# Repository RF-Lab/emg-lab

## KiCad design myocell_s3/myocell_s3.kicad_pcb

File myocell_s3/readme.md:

# multiboard myocell-s3 design

ADC + CPU board for multiboard MYOCELL design. Includes [ADS1298(4)](https://static.chipdip.ru/lib/395/DOC009395274.pdf) and [ESP32-S3-WROOM-2](https://www.espressif.com/sites/default/files/documentation/esp32-s3-wroom-2_datasheet_en.pdf). Design based on ideas from [HeartyPatch](https://hackaday.io/project/21046-heartypatch-a-single-lead-ecg-hr-patch-with-esp32), [Adafruit Feather ESP32-S3](https://learn.adafruit.com/assets/110822), [electronics-homeassistant-lightscontroll
](https://github.com/crgarcia12/electronics-homeassistant-lightscontroll) etc.

## Revision history
 Sent to rezonit 2026.03.16

* BOM: [Interactive BOM ()](https://htmlpreview.github.io/?https://github.com/RF-Lab/emg-lab/blob/main/myocell_s3/bom/ibom.html)

### Top View

### Bottom View

## Gerbers

### Top+Silkscreen

### Inner 1 (under the top)

### Inner 2

### Bottom+Silkscreen

## Dependencies

* [Espressif KiCad Library](https://github.com/espressif/kicad-libraries)

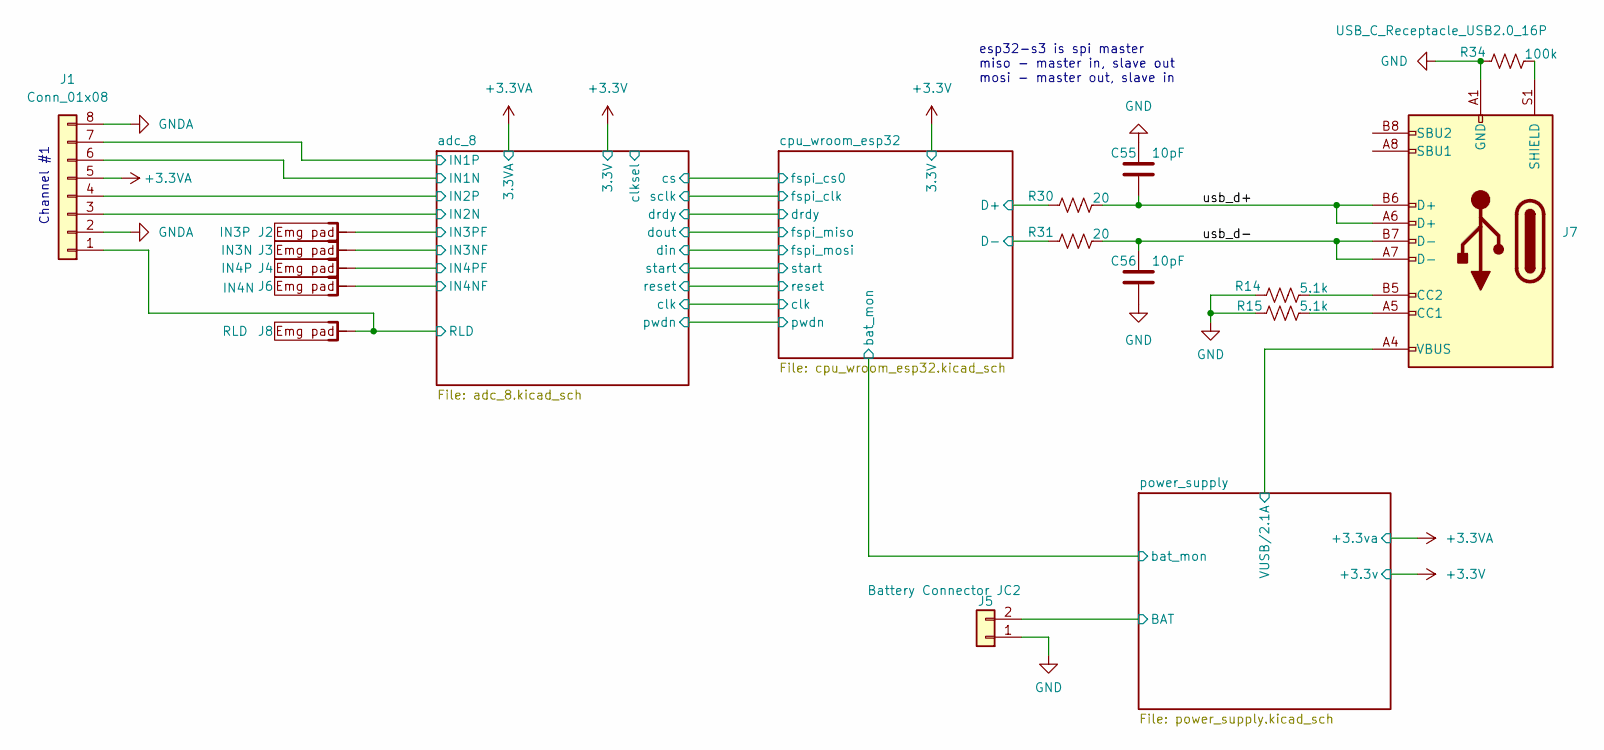
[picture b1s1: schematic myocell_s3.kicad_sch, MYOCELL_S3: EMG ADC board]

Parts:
C55, C56: 10pF; C_0805_2012Metric_Pad1.18x1.45mm_HandSolder
J1: Conn_01x08; Hirose_FH12-8S-0.5SH_1x08-1MP_P0.50mm_Horizontal
J2: IN3P; EMG_PAD_10_7
J3: IN3N; EMG_PAD_10_7
J4: IN4P; EMG_PAD_10_7
J5: Battery Connector JC2; JST_PH_S2B-PH-SM4-TB_1x02-1MP_P2.00mm_Horizontal
J6: IN4N; EMG_PAD_10_7
J7: USB_C_Receptacle_USB2.0_16P; USB_C_Receptacle_GCT_USB4110
J8: RLD; EMG_PAD_10_7
R14, R15: 5.1k; R_0805_2012Metric_Pad1.20x1.40mm_HandSolder
R30, R31: 20; R_0805_2012Metric_Pad1.20x1.40mm_HandSolder
R34: 100k; R_0805_2012Metric_Pad1.20x1.40mm_HandSolder

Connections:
+3.3VA: J1.5; also elsewhere on the board
/adc_8/RLD: J1.1, J8.1; also elsewhere on the board
/adc_8/in1+: J1.7; also elsewhere on the board
/adc_8/in1-: J1.6; also elsewhere on the board
/adc_8/in2+: J1.4; also elsewhere on the board
/adc_8/in2-: J1.3; also elsewhere on the board
/adc_8/in3f+: J2.1; also elsewhere on the board
/adc_8/in3f-: J3.1; also elsewhere on the board
/adc_8/in4f+: J4.1; also elsewhere on the board
/adc_8/in4f-: J6.1; also elsewhere on the board
/cpu_wroom_esp32/D+: R30.1; also elsewhere on the board
/cpu_wroom_esp32/D-: R31.1; also elsewhere on the board
/power_supply/BAT: J5.2; also elsewhere on the board
/power_supply/VUSB/2.1A: J7.A4 (VBUS), J7.A9 (VBUS), J7.B4 (VBUS), J7.B9 (VBUS); also elsewhere on the board
/usb_d+: C55.2, J7.A6 (D+), J7.B6 (D+), R30.2
/usb_d-: C56.1, J7.A7 (D-), J7.B7 (D-), R31.2
GND: C55.1, C56.2, J5.1, J7.A1 (GND), J7.A12 (GND), J7.B1 (GND), J7.B12 (GND), R14.1, R15.1, R34.1; also elsewhere on the board
GNDA: J1.2, J1.8; also elsewhere on the board
unnamed: J7.A5 (CC1), R15.2
unnamed: J7.B5 (CC2), R14.2
unnamed: J7.S1 (SHIELD), R34.2

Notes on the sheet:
esp32-s3 is spi master miso - master in, slave out mosi - master out, slave in
Channel #1

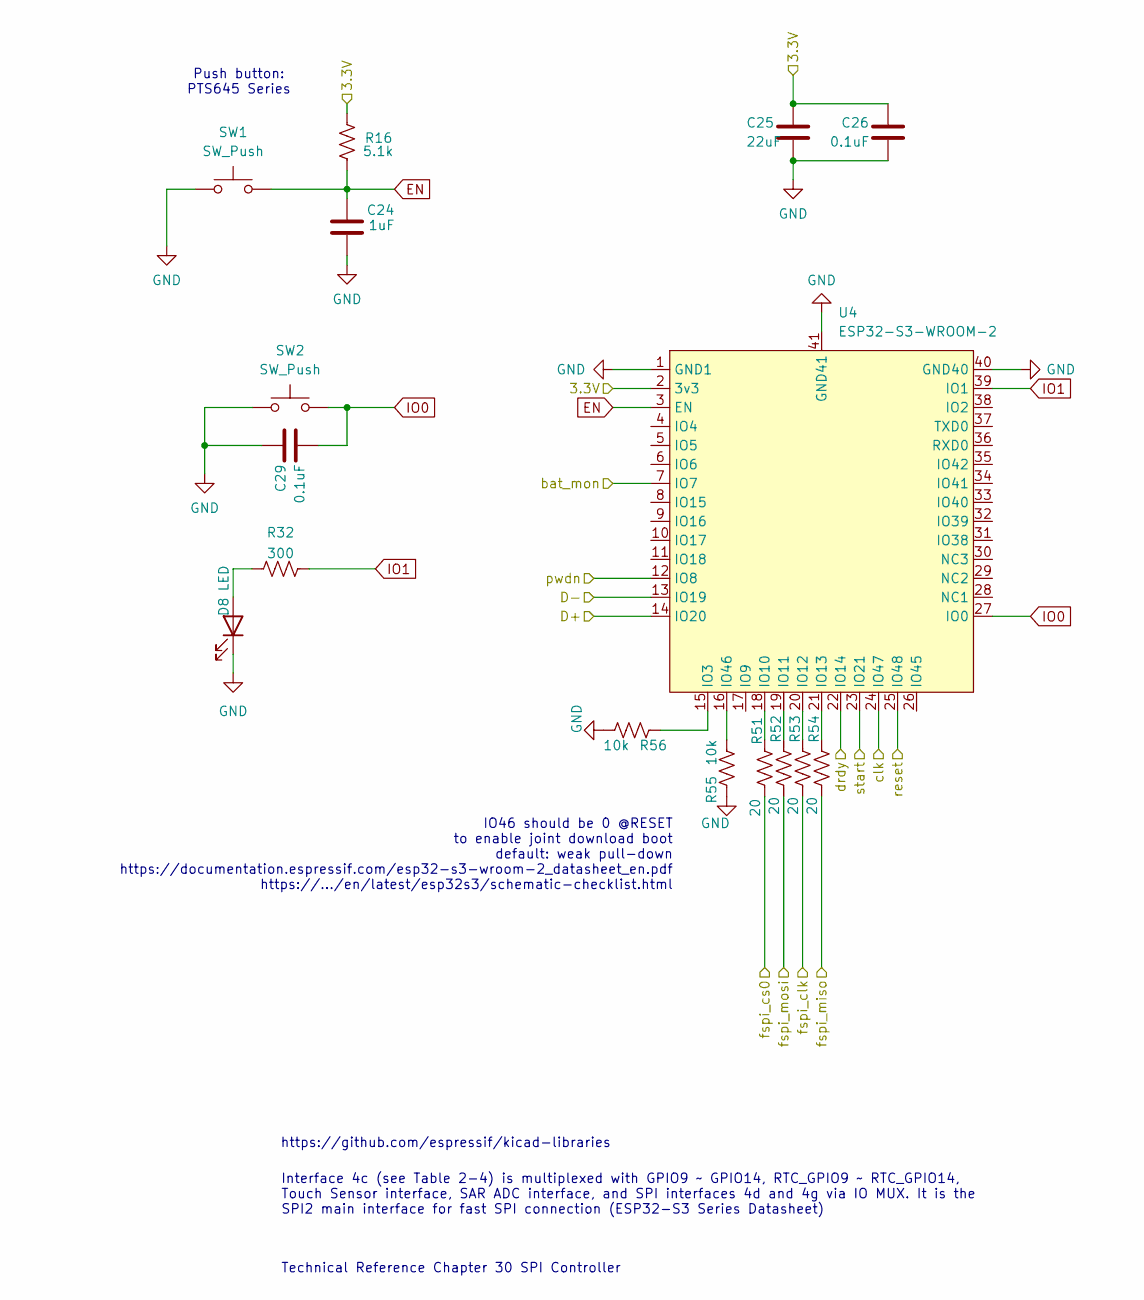
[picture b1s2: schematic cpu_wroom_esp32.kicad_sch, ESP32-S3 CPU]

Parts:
C24: 1uF; C_0805_2012Metric_Pad1.18x1.45mm_HandSolder
C25: 22uF; C_0805_2012Metric_Pad1.18x1.45mm_HandSolder
C26, C29: 0.1uF; C_0805_2012Metric_Pad1.18x1.45mm_HandSolder
D8: LED; LED_0805_2012Metric
R16: 5.1k; R_0805_2012Metric_Pad1.20x1.40mm_HandSolder
R32: 300; R_0805_2012Metric_Pad1.20x1.40mm_HandSolder
R51, R52, R53, R54: 20; R_0805_2012Metric_Pad1.20x1.40mm_HandSolder
R55, R56: 10k; R_0805_2012Metric_Pad1.20x1.40mm_HandSolder
SW1, SW2: SW_Push; SW_SPST_PTS645Sx43SMTR92
U4: ESP32-S3-WROOM-2

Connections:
+3.3V: C25.2, C26.2, R16.2, U4.2 (3v3); also elsewhere on the board
/adc_8/clk: U4.24 (IO47); also elsewhere on the board
/adc_8/cs: R51.1; also elsewhere on the board
/adc_8/din: R52.1; also elsewhere on the board
/adc_8/dout: R54.1; also elsewhere on the board
/adc_8/drdy: U4.22 (IO14); also elsewhere on the board
/adc_8/pwdn: U4.12 (IO8); also elsewhere on the board
/adc_8/reset: U4.25 (IO48); also elsewhere on the board
/adc_8/sclk: R53.1; also elsewhere on the board
/adc_8/start: U4.23 (IO21); also elsewhere on the board
/cpu_wroom_esp32/D+: U4.14 (IO20); also elsewhere on the board
/cpu_wroom_esp32/D-: U4.13 (IO19); also elsewhere on the board
/cpu_wroom_esp32/bat_mon: U4.7 (IO7); also elsewhere on the board
EN: C24.2, R16.1, SW1.2, U4.3 (EN)
GND: C24.1, C25.1, C26.1, C29.2, D8.1 (K), R55.1, R56.2, SW1.1, SW2.1, U4.1 (GND1), U4.40 (GND40), U4.41 (GND41); also elsewhere on the board
IO0: C29.1, SW2.2, U4.27 (IO0)
IO1: R32.2, U4.39 (IO1)
unnamed: D8.2 (A), R32.1
unnamed: R56.1, U4.15 (IO3)
unnamed: R51.2, U4.18 (IO10)
unnamed: R52.2, U4.19 (IO11)
unnamed: R53.2, U4.20 (IO12)
unnamed: R54.2, U4.21 (IO13)
unnamed: R55.2, U4.16 (IO46)

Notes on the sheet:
Technical Reference Chapter 30 SPI Controller
IO46 should be 0 @RESET to enable joint download boot default: weak pull-down https://documentation.espressif.com/esp32-s3-wroom-2_datasheet_en.pdf https://.../en/latest/esp32s3/schematic-checklist.html
Interface 4c (see Table 2-4) is multiplexed with GPIO9 ~ GPIO14, RTC_GPIO9 ~ RTC_GPIO14, Touch Sensor interface, SAR ADC interface, and SPI interfaces 4d and 4g via IO MUX. It is the SPI2 main interface for fast SPI connection (ESP32-S3 Series Datasheet)
Push button: PTS645 Series
https://github.com/espressif/kicad-libraries

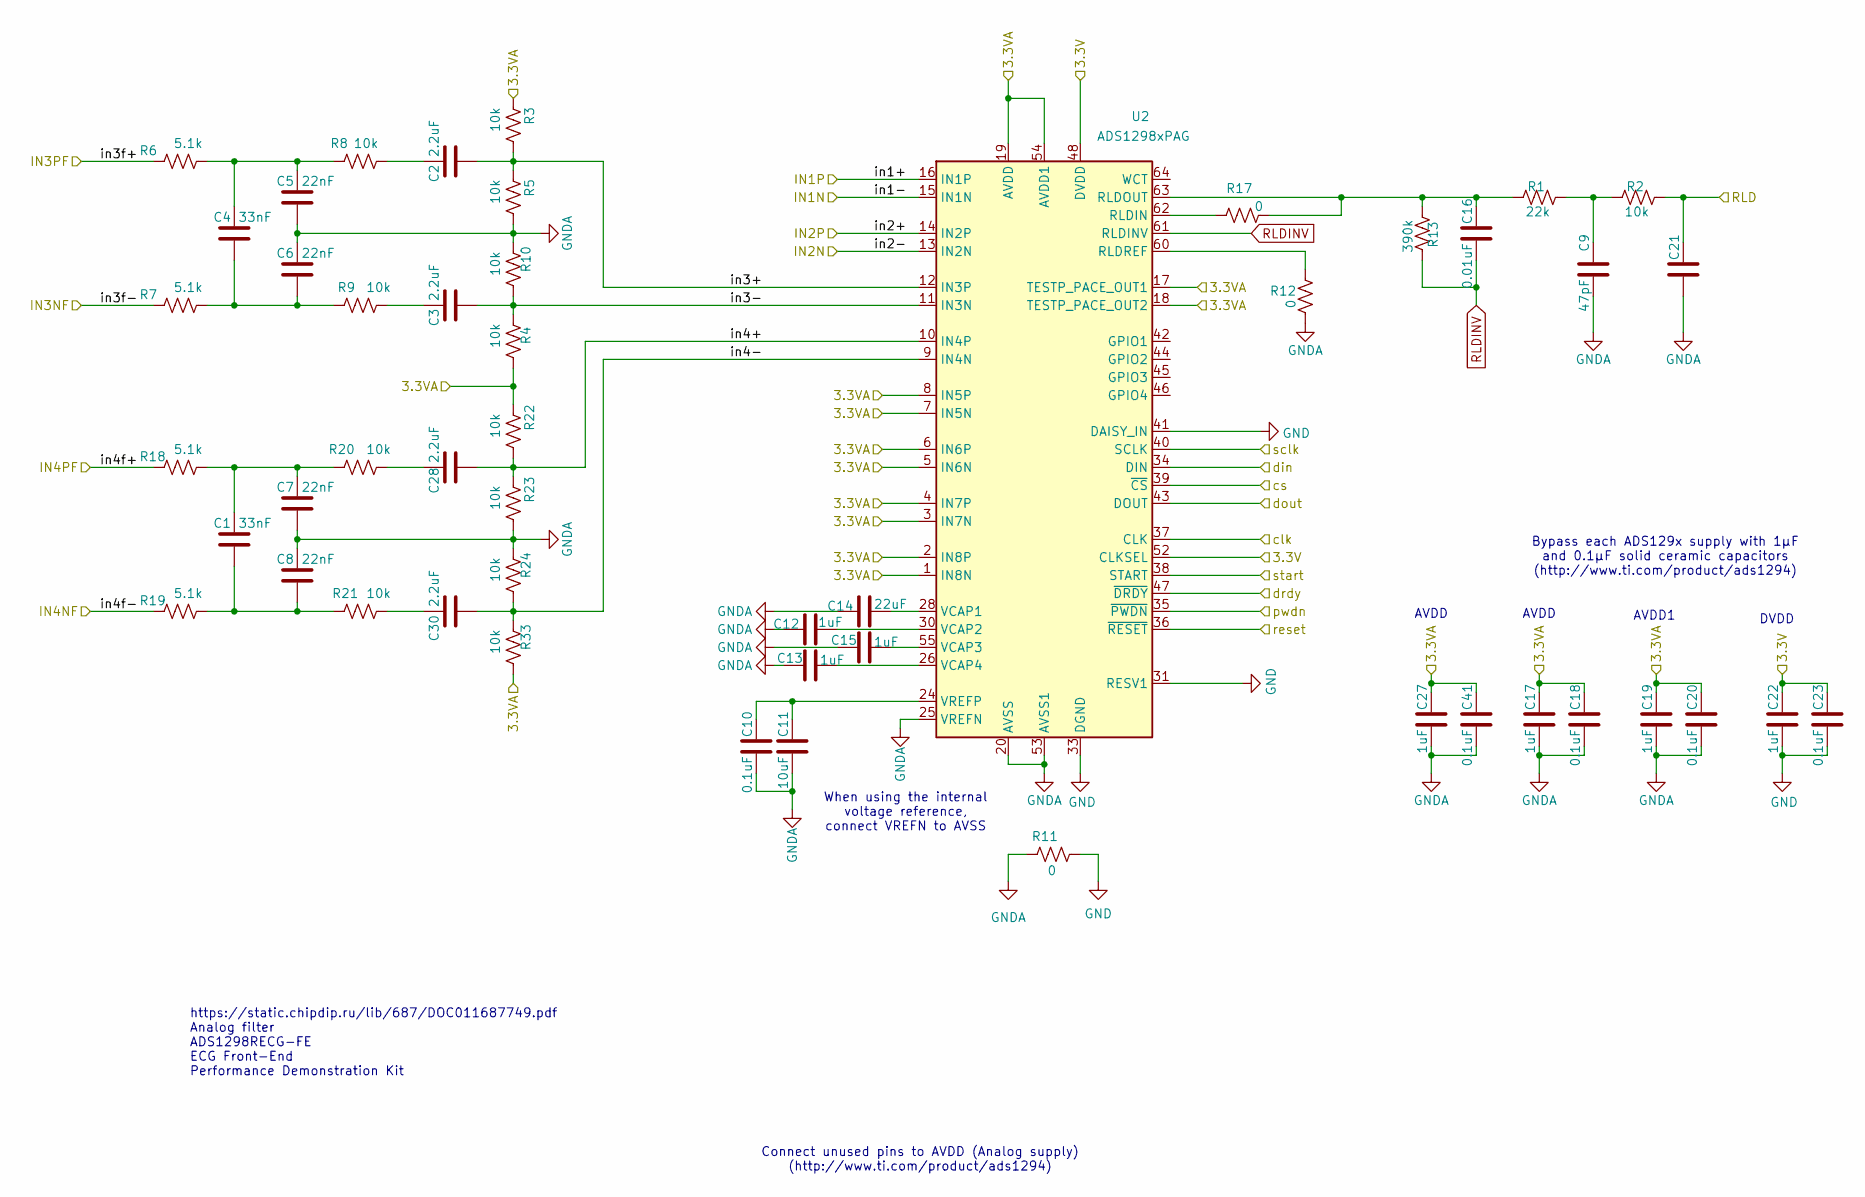
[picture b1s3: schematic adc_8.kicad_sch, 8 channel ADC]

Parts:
C1, C4: 33nF; C_0805_2012Metric_Pad1.18x1.45mm_HandSolder
C2, C3, C28, C30: 2.2uF; C_0805_2012Metric_Pad1.18x1.45mm_HandSolder
C5, C6, C7, C8: 22nF; C_0805_2012Metric_Pad1.18x1.45mm_HandSolder
C9: 47pF; C_0805_2012Metric_Pad1.18x1.45mm_HandSolder
C10, C18, C20, C23, C41: 0.1uF; C_0805_2012Metric_Pad1.18x1.45mm_HandSolder
C11: 10uF; C_0805_2012Metric_Pad1.18x1.45mm_HandSolder
C12, C13, C15, C17, C19, C22, C27: 1uF; C_0805_2012Metric_Pad1.18x1.45mm_HandSolder
C14: 22uF; C_0805_2012Metric_Pad1.18x1.45mm_HandSolder
C16: 0.01uF; C_0805_2012Metric_Pad1.18x1.45mm_HandSolder
C21: C_0805_2012Metric_Pad1.18x1.45mm_HandSolder
R1: 22k; R_0805_2012Metric_Pad1.20x1.40mm_HandSolder
R2, R3, R4, R5, R8, R9, R10, R20, R21, R22, R23, R24, R33: 10k; R_0805_2012Metric_Pad1.20x1.40mm_HandSolder
R6, R7, R18, R19: 5.1k; R_0805_2012Metric_Pad1.20x1.40mm_HandSolder
R11, R12, R17: 0; R_0805_2012Metric_Pad1.20x1.40mm_HandSolder
R13: 390k; R_0805_2012Metric_Pad1.20x1.40mm_HandSolder
U2: ADS1298xPAG; TQFP-64_10x10mm_P0.5mm

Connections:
+3.3V: C22.2, C23.2, U2.48 (DVDD), U2.50 (DVDD), U2.52 (CLKSEL); also elsewhere on the board
+3.3VA: C17.2, C18.2, C19.2, C20.2, C27.2, C41.2, R3.2, R4.1, R22.2, R33.1, U2.1 (IN8N), U2.2 (IN8P), U2.3 (IN7N), U2.4 (IN7P), U2.5 (IN6N), U2.6 (IN6P), U2.7 (IN5N), U2.8 (IN5P), U2.17 (TESTP_PACE_OUT1), U2.18 (TESTP_PACE_OUT2), U2.19 (AVDD), U2.21 (AVDD), U2.22 (AVDD), U2.54 (AVDD1), U2.56 (AVDD), U2.59 (AVDD); also elsewhere on the board
/adc_8/RLD: C21.2, R2.2; also elsewhere on the board
/adc_8/clk: U2.37 (CLK); also elsewhere on the board
/adc_8/cs: U2.39 (~CS); also elsewhere on the board
/adc_8/din: U2.34 (DIN); also elsewhere on the board
/adc_8/dout: U2.43 (DOUT); also elsewhere on the board
/adc_8/drdy: U2.47 (~DRDY); also elsewhere on the board
/adc_8/in1+: U2.16 (IN1P); also elsewhere on the board
/adc_8/in1-: U2.15 (IN1N); also elsewhere on the board
/adc_8/in2+: U2.14 (IN2P); also elsewhere on the board
/adc_8/in2-: U2.13 (IN2N); also elsewhere on the board
/adc_8/in3+: C2.2, R3.1, R5.2, U2.12 (IN3P)
/adc_8/in3-: C3.2, R4.2, R10.1, U2.11 (IN3N)
/adc_8/in3f+: R6.1; also elsewhere on the board
/adc_8/in3f-: R7.1; also elsewhere on the board
/adc_8/in4+: C28.2, R22.1, R23.2, U2.10 (IN4P)
/adc_8/in4-: C30.2, R24.1, R33.2, U2.9 (IN4N)
/adc_8/in4f+: R18.1; also elsewhere on the board
/adc_8/in4f-: R19.1; also elsewhere on the board
/adc_8/pwdn: U2.35 (~PWDN); also elsewhere on the board
/adc_8/reset: U2.36 (~RESET); also elsewhere on the board
/adc_8/sclk: U2.40 (SCLK); also elsewhere on the board
/adc_8/start: U2.38 (START); also elsewhere on the board
GND: C22.1, C23.1, R11.1, U2.31 (RESV1), U2.33 (DGND), U2.41 (DAISY_IN), U2.49 (DGND), U2.51 (DGND); also elsewhere on the board
GNDA: C5.2, C6.1, C7.2, C8.1, C9.1, C10.1, C11.1, C12.2, C13.2, C14.2, C15.2, C17.1, C18.1, C19.1, C20.1, C21.1, C27.1, C41.1, R5.1, R10.2, R11.2, R12.1, R23.1, R24.2, U2.20 (AVSS), U2.23 (AVSS), U2.25 (VREFN), U2.32 (AVSS), U2.53 (AVSS1), U2.57 (AVSS), U2.58 (AVSS); also elsewhere on the board
unnamed: C1.1, C7.1, R18.2, R20.1
unnamed: C1.2, C8.2, R19.2, R21.1
unnamed: C2.1, R8.2
unnamed: C3.1, R9.2
unnamed: C4.1, C5.1, R6.2, R8.1
unnamed: C4.2, C6.2, R7.2, R9.1
unnamed: C9.2, R1.2, R2.1
unnamed: C28.1, R20.2
unnamed: C30.1, R21.2
unnamed: R17.2, U2.62 (RLDIN)
unnamed: C16.2, R1.1, R13.1, R17.1, U2.63 (RLDOUT)
unnamed: R12.2, U2.60 (RLDREF)
unnamed: C14.1, U2.28 (VCAP1)
unnamed: C12.1, U2.30 (VCAP2)
unnamed: C15.1, U2.55 (VCAP3)
unnamed: C13.1, U2.26 (VCAP4)
unnamed: C10.2, C11.2, U2.24 (VREFP)
RLDINV: C16.1, R13.2, U2.61 (RLDINV)

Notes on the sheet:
When using the internal voltage reference, connect VREFN to AVSS
DVDD
Connect unused pins to AVDD (Analog supply) (http://www.ti.com/product/ads1294)
AVDD
AVDD1
Bypass each ADS129x supply with 1μF and 0.1μF solid ceramic capacitors (http://www.ti.com/product/ads1294)
https://static.chipdip.ru/lib/687/DOC011687749.pdf Analog filter ADS1298RECG-FE ECG Front-End Performance Demonstration Kit

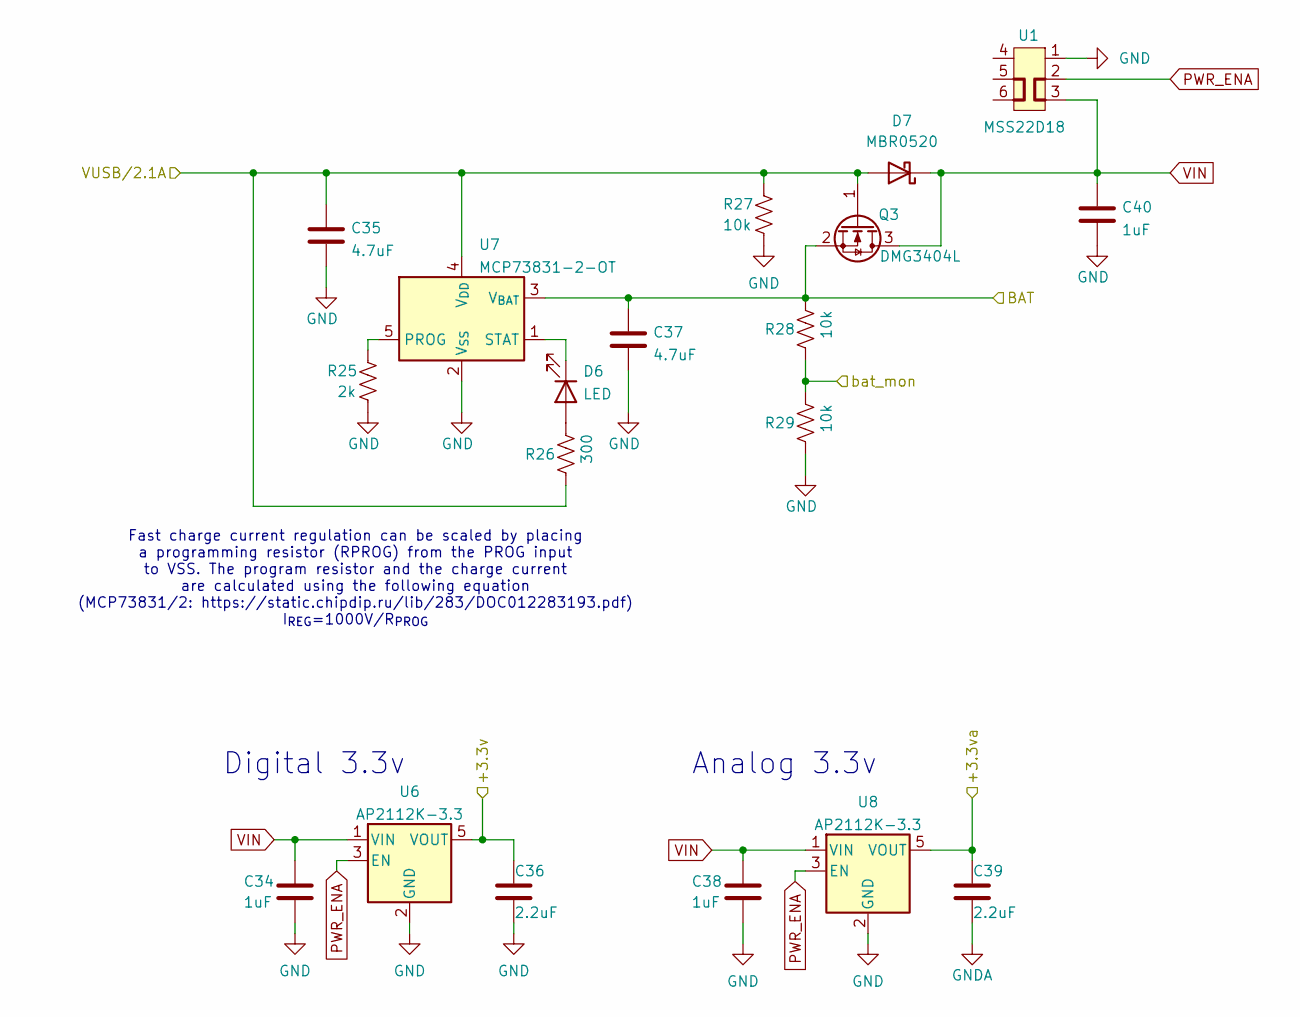
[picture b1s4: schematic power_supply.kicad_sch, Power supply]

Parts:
C34, C38, C40: 1uF; C_0805_2012Metric_Pad1.18x1.45mm_HandSolder
C35, C37: 4.7uF; C_0805_2012Metric_Pad1.18x1.45mm_HandSolder
C36, C39: 2.2uF; C_0805_2012Metric_Pad1.18x1.45mm_HandSolder
D6: LED; LED_0805_2012Metric_Pad1.15x1.40mm_HandSolder
D7: MBR0520; D_SOD-123
Q3: DMG3404L; SOT-23
R25: 2k; R_0805_2012Metric_Pad1.20x1.40mm_HandSolder
R26: 300; R_0805_2012Metric_Pad1.20x1.40mm_HandSolder
R27, R28, R29: 10k; R_0805_2012Metric_Pad1.20x1.40mm_HandSolder
U1: MSS22D18
U6, U8: AP2112K-3.3; SOT-23-5
U7: MCP73831-2-OT; SOT-23-5

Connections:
+3.3V: C36.2, U6.5 (VOUT); also elsewhere on the board
+3.3VA: C39.2, U8.5 (VOUT); also elsewhere on the board
/cpu_wroom_esp32/bat_mon: R28.1, R29.2; also elsewhere on the board
/power_supply/BAT: C37.1, Q3.2 (S), R28.2, U7.3 (V_{BAT}); also elsewhere on the board
/power_supply/VUSB/2.1A: C35.2, D7.2 (A), Q3.1 (G), R26.1, R27.2, U7.4 (V_{DD}); also elsewhere on the board
GND: C34.1, C35.1, C36.1, C37.2, C38.1, C40.1, R25.1, R27.1, R29.1, U1.1, U6.2 (GND), U7.2 (V_{SS}), U8.2 (GND); also elsewhere on the board
GNDA: C39.1; also elsewhere on the board
unnamed: D6.2 (A), R26.2
unnamed: D6.1 (K), U7.1 (STAT)
unnamed: R25.2, U7.5 (PROG)
PWR_ENA: U1.2, U6.3 (EN), U8.3 (EN)
VIN: C34.2, C38.2, C40.2, D7.1 (K), Q3.3 (D), U1.3, U6.1 (VIN), U8.1 (VIN)

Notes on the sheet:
Fast charge current regulation can be scaled by placing a programming resistor (RPROG) from the PROG input to VSS. The program resistor and the charge current are calculated using the following equation (MCP73831/2: https://static.chipdip.ru/lib/283/DOC012283193.pdf) I_{REG}=1000V/R_{PROG}
Analog 3.3v
Digital 3.3v

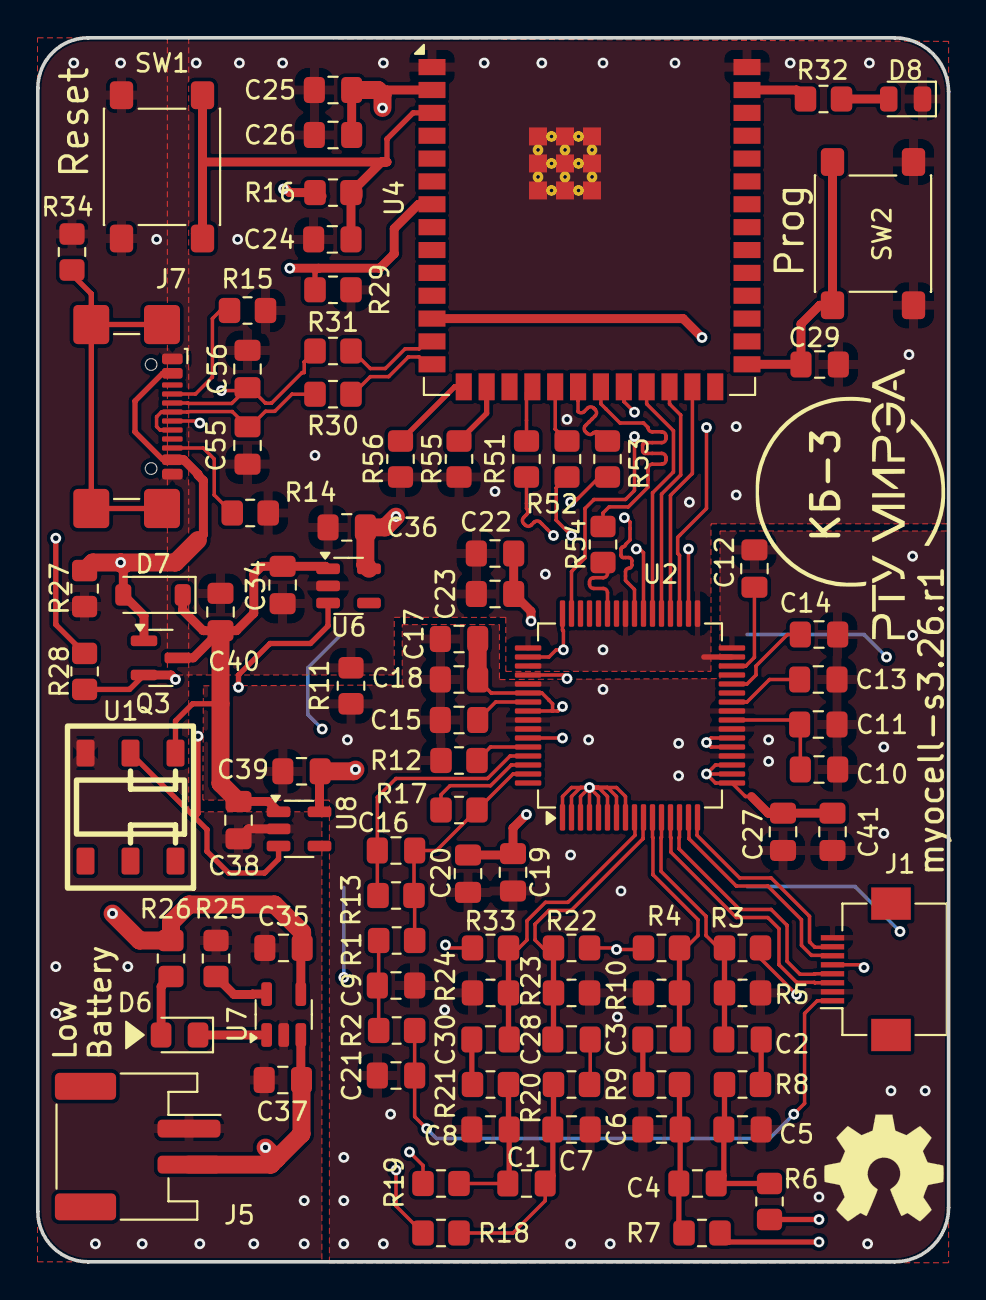
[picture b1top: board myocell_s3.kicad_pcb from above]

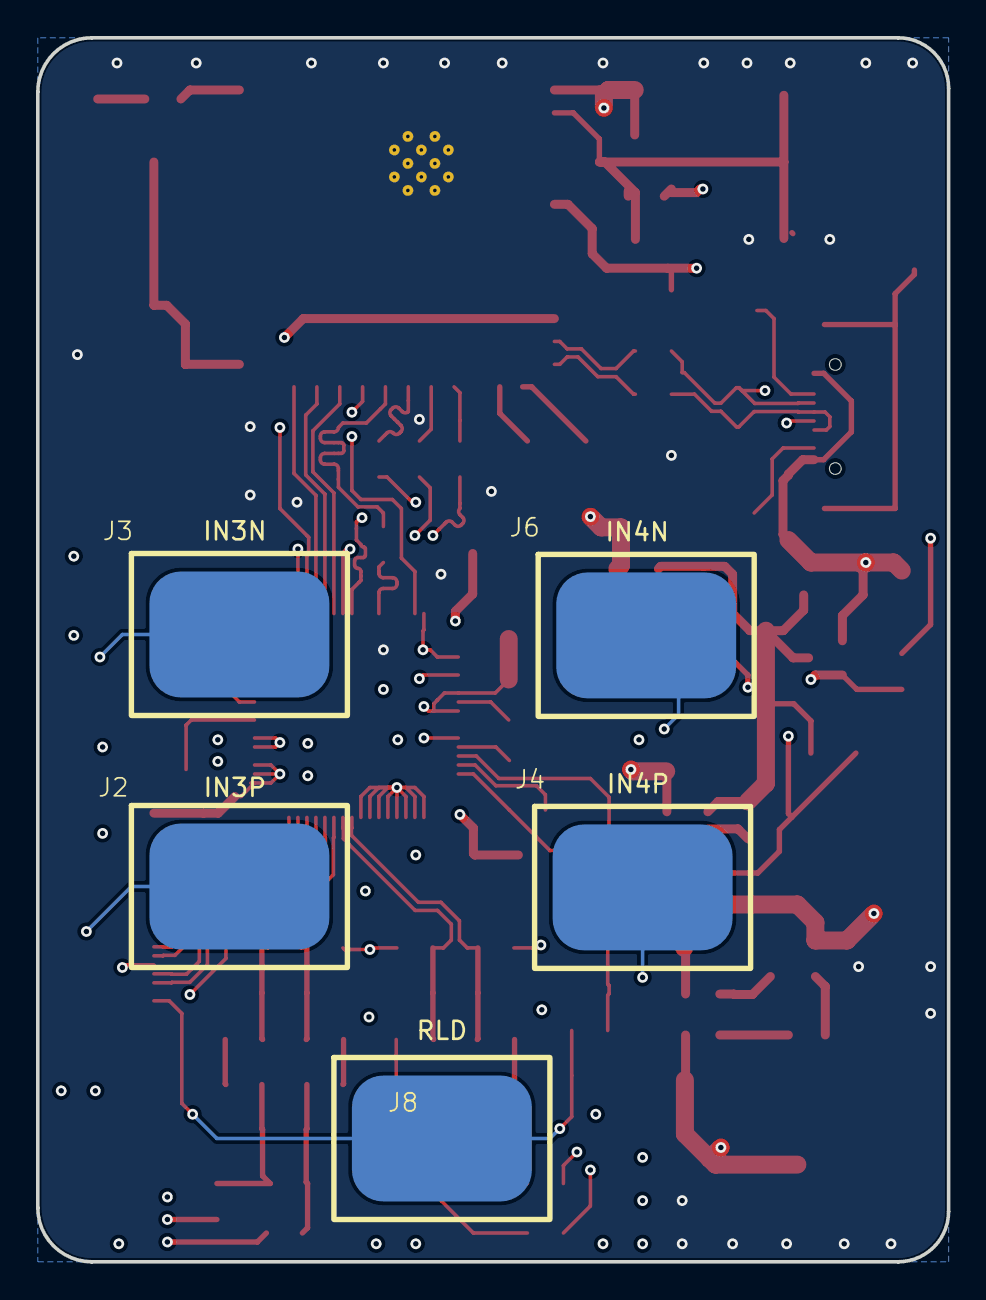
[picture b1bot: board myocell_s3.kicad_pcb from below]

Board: 4 copper layers, 50.6 x 68.0 mm, 100 parts (5 on the bottom side), 69 nets.

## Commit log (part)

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2025-05-23 initial
2025-06-04 working on emgtools signal proc
2025-06-06 muap detection modified
2025-06-09 models folder added
2025-06-10 server example added
2025-06-11 Add files via upload
    Пучков К. Д. ВКР
2025-07-31 myocell_s3 project added
2025-09-01 recovery commit
2025-10-09 working on schematic
2025-11-21 working on schematic transfer
2025-12-05 RLDINV still unconnected
2025-12-09 MSS22D18 slider switch added
2025-12-17 schematic and footprints done
2025-12-18 working on component placement
2025-12-24 working on part placement
2025-12-24 scheme main table updated
2025-12-31 amg analog interface model added
2025-12-31 working on pcb parts placement
2026-01-01 dif signal filter updated
2026-01-02 emg filters updated
2026-01-03 working on parts placement
2026-01-03 add transient settings
2026-01-11 working on components placement
2026-01-11 schematic updated: channels 3,4 is onboard now
2026-01-20 components placement
2026-01-21 component placement
2026-01-30 drdy fixed
2026-02-04 spi routed length aligned to 20mm/pm0.5mm
2026-02-05 routing
2026-02-09 tracing ADS1298
2026-02-11 tracing RLD
2026-02-13 tracing pwr
2026-02-16 tracing power
2026-02-18 tracing analogue interfaces
2026-02-27 tracing polygons
2026-02-27 tracing polygons and emg pads
2026-03-03 placing polygons
2026-03-04 polygon tuning
2026-03-09 start DRC
2026-03-10 adjust electrode positions
2026-03-15 sent to rezonit
2026-03-15 interactive BOM added
2026-03-16 schematic pdf updated
